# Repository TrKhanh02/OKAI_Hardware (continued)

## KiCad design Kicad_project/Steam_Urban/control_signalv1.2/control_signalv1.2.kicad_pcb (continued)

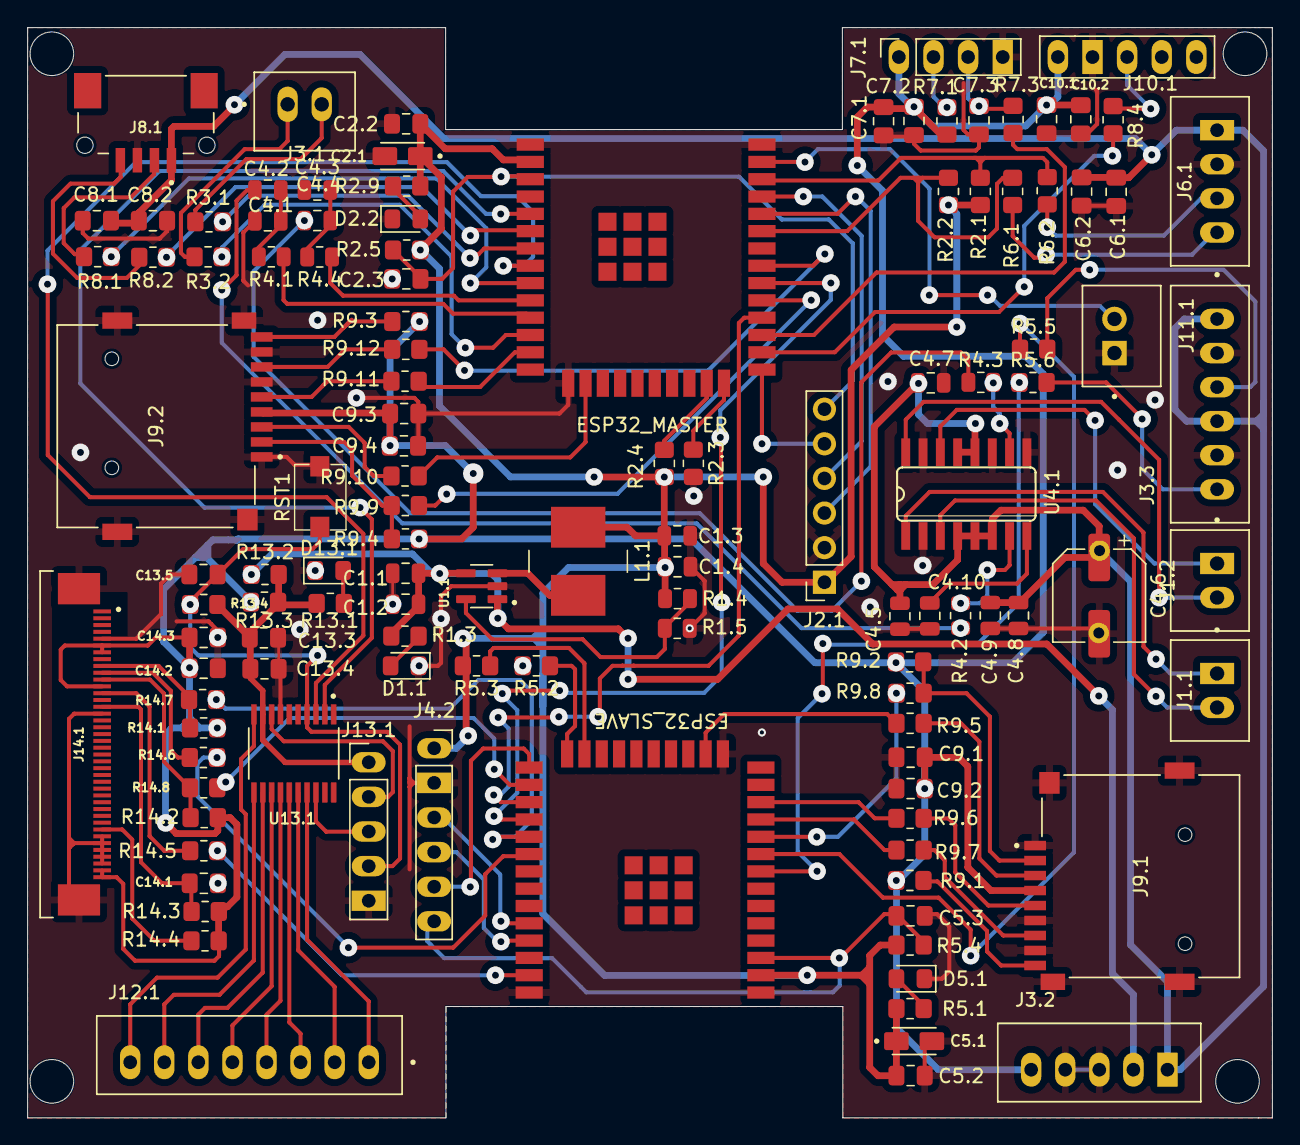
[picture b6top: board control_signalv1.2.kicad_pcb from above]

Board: 2 copper layers, 91.3 x 80.0 mm, 119 parts (0 on the bottom side), 102 nets.
